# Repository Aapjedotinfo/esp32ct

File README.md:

# ESP32CT

**16-channel CT-clamp energy monitor with P1 in/out** (ESP32, ESPHome, KiCad), and a bit of help of Claude.

[Hardware](#hardware-overview) · [Mount](#mount-3d-printed) · [Firmware](#firmware-esphome) ·
[Calibration](#calibrating-the-ct-channels) · [Build it](#building-the-board) ·
[Open points](#status-and-known-open-points) · [Support](#support-the-project)

## What it is

A through-hole PCB that turns an ESP32 into a whole-house energy monitor for
[ESPHome](https://esphome.io) and Home Assistant. Clip a current clamp on each circuit in your
meter cupboard and see what your dryer, oven, EV charger and heat pump use separately.

- **16 CT-clamp channels** through one CD74HC4067 analog multiplexer and the ESP32's ADC
- **P1 input** (RJ12) to read a Dutch/Belgian smart meter (DSMR)
- **P1 output** (RJ12) that imitates a smart meter, so an EV charger can be load-balanced
  against values you choose (developed against an Alfen charger)
- **Water meter** pulse input (inductive 5 V NPN sensor)
- **Doorbell** button input and two relay outputs via an external relay board

It started as a hand-wired board in a meter cupboard and was redesigned as rev C, a
115 × 103 mm two-layer board that anyone can order and assemble with through-hole parts only.
Free to use; if it helps you and you would like to support future projects you can
[donate via aapje.info](https://aapje.info/donations/), never required.

More views: [bottom render](hardware/esp32ct-revc/render_bottom.png), the
[schematic](hardware/esp32ct-revc/esp32ct-revc.pdf) and the
[placement drawing](hardware/esp32ct-revc/plaatsing.pdf). A photo of the installation
(clamps on the distribution board) is still to be added.

## Why this design

- **Universal channels.** All 16 channels are identical. Which circuit is clamped on
  which channel is wiring and firmware, not silkscreen.
- **Burden resistor with a jumper per channel.** Each channel has a 33 Ω burden in
  series with a jumper. Closed: bare ring CT (e.g. GTA20L1.0, 1000:1). Open: a clamp
  with a built-in burden (e.g. SCT013-015 or -050). A jumper *across* the burden would
  short the clamp, so it is wired in series.
- **Short, quiet measurement loops.** CT terminals sit opposite each other along the
  two long edges, each with its burden and jumper directly behind it.
- **1.65 V mid-rail** from an LM358 voltage follower as the bias for all channels.
- **Everything external on screw terminals** (5.00 mm), except the two RJ12 jacks.
- **Fusing.** F1 protects the whole 5 V supply; F2 (200 mA) protects the 5 V on the
  P1-output pin so a short in the charger cable does not take the board down.
- **No strapping pins in use.** The multiplexer's S1 line is on GPIO4, not GPIO12
  (a strapping pin that can stop the module from booting). A check fails the build if
  anything is ever connected to GPIO0/2/5/12/15.

## Hardware overview

| Item | Detail |
|---|---|
| Board | 115 × 103 mm, 2 layers, FR4 1.6 mm, HASL, 4 × M3 holes |
| MCU | ESP32 D1-mini-style module (footprint of the MH-ET Live MiniKit, `mhetesp32minikit`; the prototype uses an AZ-Delivery ESP32-WROOM-32 of the same form factor), at the right edge with the antenna pointing outward and a copper keep-out under it |
| Mux | HW-178 CD74HC4067 breakout, plugged into two female headers (15.24 mm row spacing) |
| CT channels | 16 × 2-pole screw terminal (YIXISI, 5.00 mm), 33 Ω burden + jumper each |
| Power | 5 V in on a screw terminal, 1 A slow fuse |
| P1 in | RJ12, BC547 inverter to GPIO18, data request on GPIO23 |
| P1 out | RJ12, GPIO17 through a BC547 inverter to an open-collector line with 4k7 pull-up to 5 V |
| Water | 5 V inductive NPN sensor, pulse on GPIO32 with 10k pull-up to 3.3 V |
| Relays | Not on the board; a two-channel Arduino relay board connects with four wires |

Full pin map: [`hardware/PINMAPPING.md`](hardware/PINMAPPING.md).

### Pin summary

| GPIO | Function |
|---|---|
| 13 / 4 / 14 / 27 | Multiplexer address S0 / S1 / S2 / S3 |
| 34 | Multiplexer signal (ADC1) |
| 18 / 23 | P1 in: RX / data request |
| 17 / 16 | P1 out: TX / data request from the charger (optional) |
| 32 | Water meter pulse |
| 33 / 25 | Doorbell relay house / garage (active low) |
| 26 | Doorbell button |

## Mount (3D printed)

The board and the external relay board sit on a printed base plate with four conical
standoffs for the main board (brass heat-set inserts) and posts for the relay board.
Latest version: **R13 "kastgaten"** (holes for the enclosure screws, 4 mm, 158 × 90 mm
pitch), 190 × 110 × 31 mm, designed in Fusion.

| File | What |
|---|---|
| [`3dhouse/ESP32CT_PCB_houder_R13_kastgaten.stl`](3dhouse/ESP32CT_PCB_houder_R13_kastgaten.stl) | print this |
| [`3dhouse/ESP32CT_PCB_houder_R13_kastgaten.step`](3dhouse/ESP32CT_PCB_houder_R13_kastgaten.step) | editable solid for any CAD program |
| [`3dhouse/ESP32CT_PCB_houder_R13_kastgaten.f3d`](3dhouse/ESP32CT_PCB_houder_R13_kastgaten.f3d) | Fusion source with the feature timeline |
| [`3dhouse/PCB Holder v5.stl`](3dhouse/PCB%20Holder%20v5.stl) | earlier version (v5), 190 × 110 × 43 mm |

**Enclosure:** the prototype lives in this junction box (clear lid):
[Amazon.nl listing](https://www.amazon.nl/Aansluitdoos-aansluitdozen-elektronicaprojectdoos-aansluitkast-transparante/dp/B0CZ6CYHLS).
The holder is made to fit it; check the inner dimensions of the box you buy against the model
before printing.

The printed holder (black, ribbed baseplate) in the enclosure. The four board standoffs
carry brass heat-set inserts, and the relay board sits on its own posts at the top.
Which exact version is shown in the photo is not recorded.

## The PCB is generated, not drawn

Schematic, netlist, placement, routing and Gerbers are all produced by scripts in
[`hardware/`](hardware/) with KiCad 10 and Freerouting:

```bash
bash build.sh
```

This regenerates the schematic, checks the netlist, runs ERC, places and routes the
board, runs DRC, and exports drawings, BOM and Gerbers. The checks it runs itself
(netlist, layout) stop the build on failure. Errors reported by KiCad's export steps are
not yet caught (known issue), so check the ERC/DRC reports and the Gerbers before
ordering. Result of the last full run: **0 ERC, 0 DRC, 0 unconnected items.**

Do not edit the KiCad files by hand or save from KiCad: the next build overwrites them.
Change the scripts (`sheets.py` for the schematic, `pcb.py` for placement) instead.

### Checks that exist because something went wrong

`check_net.py` verifies more than "the schematic agrees with itself":

- the ADC pin, the address bus, all sixteen CT chains, the bias rail, and that every
  burden jumper is in series, not in parallel;
- a list of pins that may float; everything else unconnected is an error;
- a **physical pin assignment** block that enforces the real pinout of the real parts
  (LM358, BC547, HW-178), with the source of each.

That last block exists because, during design, three symbols turned out to have
invented pin numbers (CD74HC4067, LM358, BC547). The schematic was consistent, ERC was
clean, and the board would never have worked. If you reuse the symbols, read
[`hardware/OPEN_PUNTEN.md`](hardware/OPEN_PUNTEN.md).

## Firmware (ESPHome)

The reference configuration is [`firmware/esp32ct-revc.yaml`](firmware/esp32ct-revc.yaml) (copy `firmware/secrets.yaml.example` to `secrets.yaml` first). Highlights:

- One shared `cd74hc4067` hub on GPIO13/4/14/27 with the ADC on GPIO34. Two hubs on the
  same address lines break each other's pin cache and give impossible readings.
- Per ring channel: moving average first (window 6), then quadratic noise subtraction
  `sqrt(measured² − floor²)`, then `calibrate_linear`, then a low cut-off. The order
  matters: smoothing must come before the subtraction.
- DSMR/P1 reader, water meter (`pulse_meter`), gas total, doorbell with mute switches.
- **P1 output.** Number entities on the device (`P1 Out …`): signed power per phase
  (negative = export), tariff, fallback voltage and four kWh counters. Every second it
  builds a DSMR 5 telegram with CRC-16/ARC and writes it to UART2 on GPIO17 (115200
  8N1, *not* inverted in software; the transistor does that). Voltage comes from the
  real P1 input when valid. The output only transmits while the switch `P1 Out Aan` is
  on. After a reboot it returns to the last chosen state (by design), so a board that was
  transmitting keeps transmitting.

CT calibration curves and noise floors in the configuration belong to one installation
(ring CTs with 33 Ω, about 0.031 V/A fitted). **Measure your own.**

## Calibrating the CT channels

The board measures the voltage across the burden, not current. Firmware turns that
voltage into amperes per channel. Procedure used in this project:

1. **Start from the theoretical sensitivity** (volts per ampere at the ADC input):

   | Clamp | V/A |
   |---|---|
   | ring 1000:1 with 33 Ω burden (jumper closed) | 0.033 theoretical, about 0.031 fitted |
   | SCT013-015 (15 A / 1 V, built-in burden, jumper open) | 0.067 |
   | SCT013-050 (50 A / 1 V), one pass of the conductor | 0.02 |
   | SCT013-050, two passes (both in the same direction, insulated wire only) | 0.04 |

   Amps = measured volts ÷ V/A (for the 50 A clamp: ÷ (0.02 × number of passes)).
   These are theoretical values; real clamps deviate, so always measure.
2. **Measure the noise floor** with the conductor carrying no load: take the RMS
   reading of the channel (volts). On this installation about 0.042 V on the ring
   channels, which is roughly 1.4 A. Higher sensitivity clamps give a lower floor in
   amps (about 0.6 A for the 15 A clamp), but the floor is installation dependent.
3. **Filter order matters:** moving average first, then quadratic noise subtraction
   `signal = sqrt(measured² − floor²)`, then the linear calibration, then a cut-off
   (0.04 A here). Subtracting before smoothing works on an unstable value and gives
   unusable results.
4. **Fit the curve with known loads.** Switch on a load whose current you know or can
   measure with a reference (a plug-in energy meter or a Shelly, in this project) and
   read the channel's smoothed voltage. Use several loads across the range and enter
   the pairs in ESPHome as `calibrate_linear` points (voltage → amps), for example
   0.006 → 0, 0.109 → 3.45, 0.178 → 5.19, 0.263 → 8.48 for one ring channel.
5. **Re-check after any change** of clamp, burden or jumper. Closed or open jumper
   gives a completely different curve.
6. **Power** is `current × 230 V`. There is no voltage measurement and no phase
   information, so power factor is ignored and **direction cannot be seen**. A group
   with both load and generation shows the difference.

The ADC of an ESP32 is not linear near its limits; stay well within the clamp's range
for the channel (see the table below) and calibrate at the currents you care about.

| Clamp | Approximate range at the ADC |
|---|---|
| ring with 33 Ω | about 35 A |
| SCT013-015 | about 17 A |
| SCT013-050, one pass | about 58 A |
| SCT013-050, two passes | about 29 A |

Ranges and noise floors for the SCT013 clamps are estimates, not measurements.

## Building the board

**Ordering.** The Gerbers work with any PCB fab. Disclosure: I use [Aisler](https://aisler.net)
and earn shop credit when you order through my referral code `MakeInEurope-VYPFM` (you get
€10 off your first order). This is not an endorsement by Aisler.

1. Order `esp32ct-revc-gerbers.zip` from any fabricator (2 layers, 1.6 mm, HASL).
2. Check before you order, see [`hardware/OPEN_PUNTEN.md`](hardware/OPEN_PUNTEN.md):
   - row spacing of your HW-178 (15.24 mm)
   - wire entry direction and width of your screw terminals (≤ 10.7 mm per block;
     terminals sit on a 10.795 mm pitch)
   - GPIO16/17 on your MiniKit
   - that your relay board switches properly at 3.3 V on IN
3. Flash the ESP32 over USB **before** the HW-178 goes in; the USB connector is blocked
   afterwards. Later updates go over the air.
4. For clamps with a built-in burden (SCT013) leave the channel jumper **open**; for
   ring CTs close it. A channel with no clamp should keep its jumper **closed**,
   otherwise the mux input floats.

## Network security

The example configuration has no OTA password and no web-server login, which is common
on a trusted home network. Anyone who can reach the device can update its firmware and
operate it. Add `password:` to `ota` and `auth:` to `web_server` (with entries in your
`secrets.yaml`) if your network is not trusted.

## Documentation language

The README is in English. The detailed hardware notes in `hardware/` (`README.md`,
`OPEN_PUNTEN.md`, `PINMAPPING.md`, `PCB_BESCHRIJVING.md`) are still in Dutch; translations
are welcome. Silkscreen text on the board is Dutch too.

## Status and known open points

Rev C has been built and is running, but this is a hobby project made for one house.
Honestly open:

- The firmware builds a DSMR 5 telegram with CRC-16/ARC for the P1 output, but the
  actual output signal, a loopback test into the board's own P1 input, and
  acceptance by the EV charger are all **unverified**.
- A CT sees magnitude only, not direction. A circuit with both load and generation
  (e.g. solar on the same group) reads the *difference*.
- Some values in the power and P1 sheets are conventional designs, not measured from
  the original board: the 1.65 V divider, LM358 supply (3.3 V vs 5 V), bulk
  capacitors, the P1 inverter resistors, and whether P1 data-request may connect
  directly to a 3.3 V GPIO.
- Screw-terminal wire entry direction was derived from the footprint, not measured.
- Whether the charger expects DSMR 5 (115200 8N1) or DSMR 2/3 (9600 7E1).
- **Electrical safety.** The board itself only carries extra-low voltage, but CTs go
  around mains conductors; clamp only insulated conductors. A bare ring CT (1000:1,
  current output) with an open secondary develops dangerous voltage while primary
  current flows. On this board, opening a channel jumper (JP101-JP116) on a **ring-CT
  channel** is exactly that case: never open it while the conductor carries current.
  Only clamps with a built-in burden (SCT013 xA/1V) may have the jumper open.

## Repository layout

```
hardware/        KiCad generation scripts, checks, build.sh, docs
  esp32ct-revc/  generated KiCad project, Gerbers, drawings, BOM
  lib/           third-party footprints with provenance
firmware/        ESPHome configuration (rev C) and secrets.yaml.example
3dhouse/         3D-printable mount (STL)
```

## Licence

See [`LICENSE.md`](LICENSE.md).

| Part | Licence |
|---|---|
| Hardware, documentation, photos, 3D mount | [CERN-OHL-W-2.0](https://ohwr.org/cern_ohl_w_v2.txt) |
| Firmware (`firmware/`) | MIT |
| Third-party parts in `hardware/lib/` | their own licences (see Credits) |

You may build, use, modify and sell boards from these files. Changes to the hardware
design must be shared under the same licence. The hardware is provided without any
warranty; you are responsible for safe installation on your own mains wiring.

## Support the project

This board is a hobby project, free to use. If it saved you time or money and you
would like to help fund future projects, a donation is very welcome (never required):

- Donate via [aapje.info/donations](https://aapje.info/donations/)

Building a board and reporting what you found (photos, measurements, fixes) helps
just as much: please open an issue or a pull request.

## Credits and third-party material

- ESP32 MiniKit footprint from
  [r0oland/ESP32_mini_KiCad_Library](https://github.com/r0oland/ESP32_mini_KiCad_Library)
  (Apache-2.0), copy and licence text in `hardware/lib/`.
- Screw-terminal footprint derived from KiCad's MaiXu MX126 with a tighter courtyard.
- Symbols for LM358 and BC547 verified against KiCad's own libraries; HW-178 pinout
  verified against SparkFun's board file.
- Built with KiCad 10, Freerouting and ESPHome.

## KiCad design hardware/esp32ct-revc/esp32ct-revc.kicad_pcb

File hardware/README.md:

# esp32ct — hardware

KiCad-project voor **rev C** van het CT-bord: schema, netlist en een volledig
gerout bord, tot en met de Gerbers voor de printfabriek. Rev C is rev B met de
waarden van alle onderdelen op de zeefdruk en een liggende F2; elektrisch en
qua pinbezetting zijn ze gelijk. Basis is het huidige
bord, gereconstrueerd uit de draaiende firmware en uit opgave van de eigenaar;
er lag geen eerder ontwerp.

Gebouwd en gecontroleerd met **KiCad 10.0.6**. `build.sh` pakt zelf de nieuwste
installatie die het vindt; zet `KICAD_DIR` als je een andere wilt afdwingen.
Let op: het bord wordt door pcbnew 10 weggeschreven in het 10-formaat en is
daarmee niet meer met KiCad 9 te openen. Het schema schrijft de generator zelf,
nog in het 9-formaat, en dat leest 10 probleemloos.

Lees `OPEN_PUNTEN.md` voordat je hier iets uit overneemt. Daarin staat wat
vaststaat, wat aangenomen is, en wat er verandert ten opzichte van het bord dat
er nu hangt.

Wat je niet over het hoofd moet zien:

- **Bestelklaar:** `esp32ct-revc/esp32ct-revc-gerbers.zip`. 115 × 103 mm,
  2 lagen, FR4 1,6 mm, HASL (loodvrij mag).
- **Meet eerst je HW-178 en een schroefklem na** — zie `OPEN_PUNTEN.md` voor
  wat je vóór het bestellen controleert. De klemmen staan vrijwel tegen elkaar.
- **De relais zitten op een los Arduino-relaisbordje.** Die zijn actief-laag;
  de firmware heeft dan `inverted: true` nodig, anders rinkelt de bel bij elke
  reboot.
- **16 kanalen, één multiplexer.** De laadpaal wordt voortaan via de
  nagebootste P1-uitgang gestuurd in plaats van met CT's gemeten.
- **Firmware voor rev C:** `PINMAPPING.md` heeft de pinbezetting per GPIO en
  per connector, en wat er in `firmware/esp32ct-revc.yaml` moet veranderen.

## Openen

```bash
"/c/Program Files/KiCad/10.0/bin/kicad.exe" esp32ct-revc/esp32ct-revc.kicad_pro
```

Of blader door `esp32ct-revc/esp32ct-revc.pdf` (schema) en `plaatsing.pdf`
(bord) als je alleen wilt kijken.

## Bladindeling

| Blad | Inhoud |
|---|---|
| 1 | Overzicht en ESP32 — de complete pinbezetting |
| 2 | Voeding en VBIAS — 5 V in, de 1,65 V middenrail |
| 3 | Multiplexer — voetje voor het HW-178-breakout (CD74HC4067) |
| 4 | CT-kanalen 1-16, elk met burden en jumper |
| 5 | P1 slimme meter — ingang vanaf de echte meter |
| 6 | Deurbel en watermeter |
| 7 | P1-uitgang naar de laadpaal |

Alle bladen zijn onderling verbonden met globale labels; er zijn geen
hiërarchische pinnen. Een net met dezelfde naam is overal hetzelfde net.

## Schema én PCB zijn gegenereerd, niet getekend

`gen_sch.py` bevat de symbolen en de KiCad-primitieven, `sheets.py` beschrijft
het schema, `pcb.py` de plaatsing. **Pas de KiCad-bestanden niet met de hand
aan** — wijzig het script en bouw opnieuw, anders is je wijziging bij de
volgende run weg.

Dat is bewust: zestien identieke kanalen met de hand tekenen én plaatsen is
foutgevoelig, en het ontwerp verandert nog. Nu is de bron van waarheid een
leesbare lijst.

```bash
python3 sheets.py && python3 check_net.py
```

`check_net.py` controleert de geëxporteerde netlist op de verbindingen die echt
moeten kloppen: de ADC-pin, de adresbus, alle zestien CT-ketens, de VBIAS-rail,
en of de burden-jumper wel in serie staat en niet parallel. Het faalt hard als
er iets niet klopt, zodat een fout in de generator niet stilletjes in het
ontwerp blijft staan.

Daarnaast staat er een lijst van pinnen die los **mogen** hangen. Alles wat
daarbuiten valt is een fout. Die controle is er niet voor niets: tijdens het
bouwen verbraken drie verbindingen stilletjes doordat een draad midden op een
andere draad eindigde. In KiCad verbindt dat niet — ook niet met een junction
erbij — en het schema zag er gewoon goed uit.

En er is een blok **fysieke pinbezetting**: welke pin van het échte onderdeel
op welk net hoort, met de bron erbij (KiCad's eigen symbolen voor de LM358 en
BC547, SparkFun's bordbestand voor het HW-178). Alle andere controles kijken
of het schema met zichzelf klopt; deze kijkt of het klopt met de onderdelen die
je erop soldeert. Hij bestaat omdat drie symbolen verzonnen pinnummers bleken
te hebben — zie `OPEN_PUNTEN.md`. Nagegaan door de oude fouten tijdelijk terug
te zetten: hij vangt ze alle drie.

## De PCB

`pcb.py` bouwt `esp32ct-revc.kicad_pcb` uit de netlist: bordomtrek, alle
footprints op hun plek, elk pad op het juiste net, netklassen, de
massavlakken, het antenneverbod, montagegaten en de zeefdruk. Daarna legt
`freeroute.py` de banen met Freerouting. Het bord wordt bij elke build vanaf
nul geplaatst en gerout; er zit geen handwerk in.

Beide scripts draaien op de Python van KiCad, niet die van het systeem, want
alleen die heeft `pcbnew`. `build.sh` regelt dat zelf.

Bord: **115 × 103 mm**, dubbelzijdig, alles doorstekend, 77 onderdelen plus
4 montagegaten (M3). De indeling:

| Waar | Wat |
|---|---|
| boven- en onderrand | 16 CT-klemmen, acht per zijde, met staande burden en jumper er direct achter; de belknop J6 als negende klem onderaan |
| linkerrand | POWER IN (J1, met zekering F1 erachter), WATER (J3/J9), RELAIS (J4/J5); de 1,65 V-middenrail erachter |
| midden | het HW-178-voetje, precies tussen de twee CT-rijen |
| rechterrand | de twee RJ12's onder elkaar (P1 INPUT boven, P1 OUTPUT onder), met hun P1-onderdelen ernaast (ook F2/JP1: 5 V naar P1 OUT); daaronder de ESP32 met de antenne naar buiten |

De CT-klemmen staan met opzet tegenover elkaar langs de lange zijden, met hun
burden en jumper er meteen achter. Zo blijft de lus van klem naar burden kort;
dat is de gevoelige plek in deze meting. De klemmen staan op 10,795 mm steek,
~0,3 mm tussen de bodies; daarvoor is er een eigen footprint met de courtyard
op de body (`lib/MX126_2P_5mm_krap`).

Onder de antenne van de ESP32 ligt een **verbodsgebied voor koper**, zodat de
massavlakken de WiFi niet verstikken.

### Banen en massa

Freerouting legt alle verbindingen, **ook GND als gewone banen**. Daarbovenop
ligt op beide lagen een GND-vlak. Freerouting krijgt die vlakken bewust niet
te zien: met een vlak erbij legt hij geen enkele GND-baan, en vielen er steeds
GND-pads op een eilandje tussen de signaalbanen. Blijft er toch een
GND-verbinding open, dan beslist de DRC na het gieten van de vlakken of die via
het vlak dicht is. Een open verbinding op elk ander net stopt de build.

Freerouting geeft niet elke run hetzelfde resultaat. Daarom draaien de DRC en
de controles bij elke build opnieuw, en telt een eerdere geslaagde run niet.

### Aannames over de randconnectoren

**Schroefklemmen:** de draadinvoer staat naar buiten, op de aanname dat die aan
de **+Y-kant** van de footprint zit. Dat volgt uit de footprint zelf — de pads
liggen 3,80 mm van die rand en 4,00 mm van de andere, en de fab-laag tekent
daar een aparte band — maar het is niet aan een echt blokje nagemeten. Klopt
het niet, zet `INVOER` bovenin `pcb.py` op `0` en alle klemmen draaien in één
keer om.

**RJ12's:** de stekker gaat er aan de +Y-kant in. Dat is wél zeker: de pinnen
zitten achterin, op Y = 0 tot 2,5 mm, en aan de pinkant kan geen stekker in.

## Alles opnieuw uitvoeren

```bash
bash build.sh
```

Dat genereert het schema, controleert de netlist, draait de ERC, plaatst en
rout het bord, draait de DRC, en maakt tekeningen, renders, stuklijst en
Gerbers. Het stopt bij de eerste fout: een ERC of DRC met ook maar één melding,
of een verbinding die open blijft, levert geen Gerbers op. De huidige stand:
**0 ERC-meldingen, 0 DRC-meldingen, 0 onverbonden items.**

Freerouting (en Java 25) staan gebruikersbreed in
`%LOCALAPPDATA%\Programs\freerouting`; zet `FREEROUTING_JAR` om een andere te
gebruiken. De oude eigen router `route.py` werkt nog, maar de build gebruikt
hem niet meer.

Had je het project open in KiCad: sluit het en open het opnieuw. **Sla niet op
vanuit KiCad** — dat schrijft over de gegenereerde bestanden heen, en bij de
volgende build is het weer weg.

## Gegenereerde bestanden

In `esp32ct-revc/` staan naast de schema- en bordbestanden ook:

| Bestand | Wat |
|---|---|
| `esp32ct-revc-gerbers.zip` | Gerbers + boorbestanden, dit upload je bij de fabriek |
| `productie/` | dezelfde bestanden los |
| `render_top.png`, `render_bottom.png` | 3D-aanzicht van beide kanten |
| `plaatsing.pdf`, `bovenkant.pdf`, `onderkant.pdf` | bordtekeningen; de onderkant gespiegeld |
| `esp32ct-revc.pdf` | het schema |
| `bom.csv` | stuklijst |
| `esp32ct-revc.net`, `erc.txt`, `drc.txt` | netlist en controlerapporten |

Die worden allemaal opnieuw gemaakt door `build.sh` en zijn dus geen handwerk.

De symbolen staan in `esp32ct.kicad_sym`, een projecteigen bibliotheek. Het
project verwijst daar via `sym-lib-table` naar, dus het opent op elke machine
zonder dat je iets hoeft te installeren.

## Onderdelen van derden

De footprint van de ESP32-module komt uit
[r0oland/ESP32_mini_KiCad_Library](https://github.com/r0oland/ESP32_mini_KiCad_Library),
Apache License 2.0. De bron staat in `lib/` samen met de licentietekst;
`sheets.py` kopieert hem naar `esp32ct.pretty/`.

Belangrijk gevolg: **de pinnummers van U1 zijn de echte padnummers van de
module, niet de GPIO-nummers.** GPIO34 is pad 11, GPIO35 is pad 7, GPIO13 is
pad 18, enzovoort. De vertaaltabel staat bovenaan `check_net.py` en in
`sheets.py` als `NET_PER_PAD`. Zonder die nummering sluit het symbool niet aan
op de footprint.

De klemmenblokken zijn het type dat de eigenaar op voorraad heeft: YIXISI
2-polig met **5,00 mm steek** (het blauwe KF301-type) — nadrukkelijk geen
5,08 mm. De footprint is een kopie van KiCad's MaiXu MX126 met een krappere
courtyard en zeefdruk; zie `lib/MX126_2P_5mm_krap.HERKOMST.txt`.

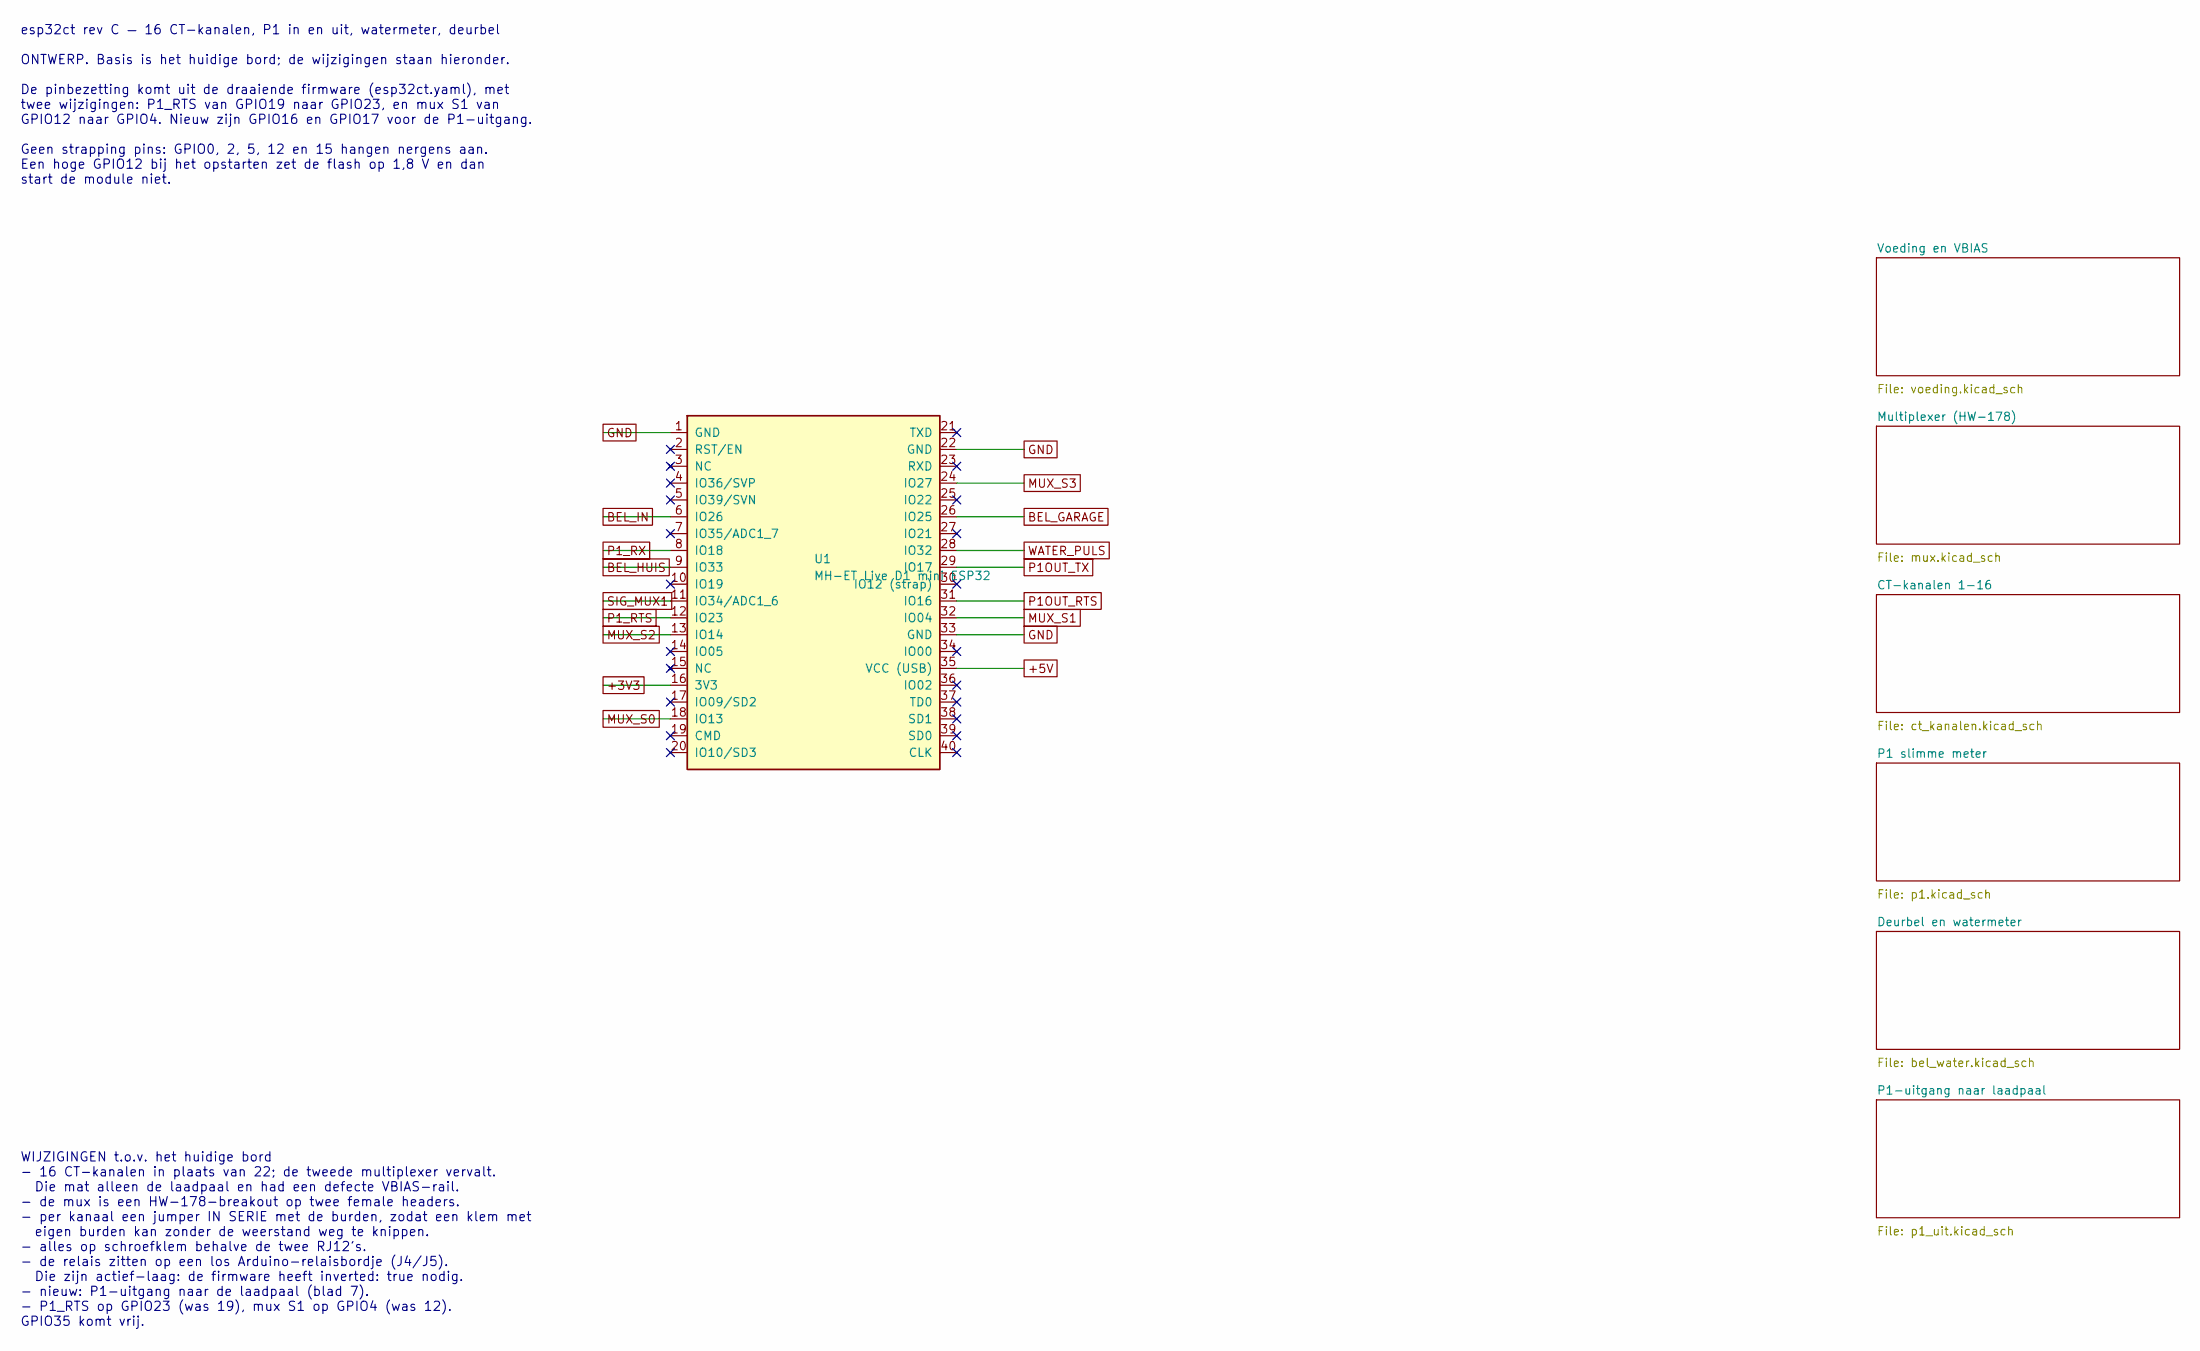
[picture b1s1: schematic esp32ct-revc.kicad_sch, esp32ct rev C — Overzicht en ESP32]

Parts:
U1: MH-ET Live D1 mini ESP32; ESP32_mini

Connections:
+3V3: U1.16 (3V3); also elsewhere on the board
+5V: U1.35 (VCC (USB)); also elsewhere on the board
BEL_GARAGE: U1.26 (IO25); also elsewhere on the board
BEL_HUIS: U1.9 (IO33); also elsewhere on the board
BEL_IN: U1.6 (IO26); also elsewhere on the board
GND: U1.1 (GND), U1.22 (GND), U1.33 (GND); also elsewhere on the board
MUX_S0: U1.18 (IO13); also elsewhere on the board
MUX_S1: U1.32 (IO04); also elsewhere on the board
MUX_S2: U1.13 (IO14); also elsewhere on the board
MUX_S3: U1.24 (IO27); also elsewhere on the board
P1OUT_RTS: U1.31 (IO16); also elsewhere on the board
P1OUT_TX: U1.29 (IO17); also elsewhere on the board
P1_RTS: U1.12 (IO23); also elsewhere on the board
P1_RX: U1.8 (IO18); also elsewhere on the board
SIG_MUX1: U1.11 (IO34/ADC1_6); also elsewhere on the board
WATER_PULS: U1.28 (IO32); also elsewhere on the board

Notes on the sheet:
esp32ct rev C — 16 CT-kanalen, P1 in en uit, watermeter, deurbel ONTWERP. Basis is het huidige bord; de wijzigingen staan hieronder. De pinbezetting komt uit de draaiende firmware (esp32ct.yaml), met twee wijzigingen: P1_RTS van GPIO19 naar GPIO23, en mux S1 van GPIO12 naar GPIO4. Nieuw zijn GPIO16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
WIJZIGINGEN t.o.v. het huidige bord - 16 CT-kanalen in plaats van 22; de tweede multiplexer vervalt. Die mat alleen de laadpaal en had een defecte VBIAS-rail. - de mux is een HW-178-breakout op twee female headers. - per kanaal een jumper IN SERIE met de burden, zodat een klem met eigen burden kan 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

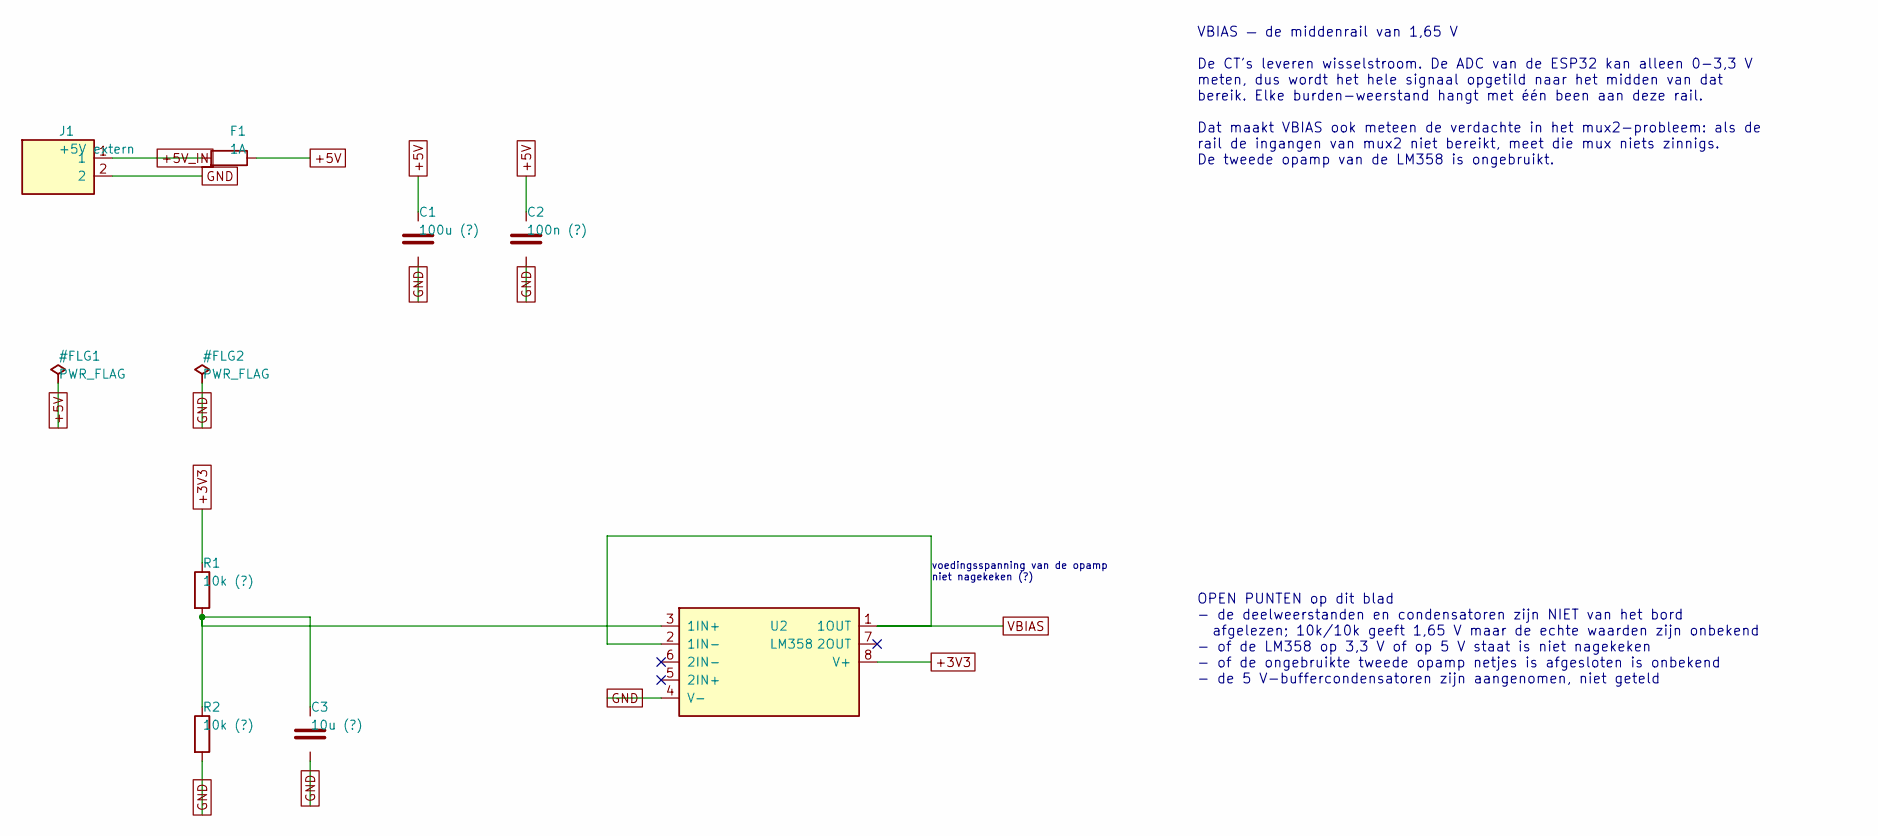
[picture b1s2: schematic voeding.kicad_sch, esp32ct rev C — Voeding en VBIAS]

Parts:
C1: 100u (?); CP_Radial_D6.3mm_P2.50mm
C2: 100n (?); C_Disc_D5.0mm_W2.5mm_P5.00mm
C3: 10u (?); CP_Radial_D6.3mm_P2.50mm
F1: 1A; R_Axial_DIN0207_L6.3mm_D2.5mm_P10.16mm_Horizontal
J1: +5V extern; MX126_2P_5mm_krap
R1, R2: 10k (?); R_Axial_DIN0207_L6.3mm_D2.5mm_P10.16mm_Horizontal
U2: LM358; DIP-8_W7.62mm

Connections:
+3V3: R1.1, U2.8 (V+); also elsewhere on the board
+5V: C1.1, C2.1, F1.2; also elsewhere on the board
+5V_IN: F1.1, J1.1
GND: C1.2, C2.2, C3.2, J1.2, R2.2, U2.4 (V-); also elsewhere on the board
unnamed: C3.1, R1.2, R2.1, U2.3 (1IN+)
VBIAS: U2.1 (1OUT), U2.2 (1IN-); also elsewhere on the board

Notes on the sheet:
voedingsspanning van de opamp niet nagekeken (?)
VBIAS — de middenrail van 1,65 V De CT's leveren wisselstroom. De ADC van de ESP32 kan alleen 0-3,3 V meten, dus wordt het hele signaal opgetild naar het midden van dat bereik. Elke burden-weerstand hangt met één been aan deze rail. Dat maakt VBIAS ook meteen de verdachte in het mux2-probleem: als 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
OPEN PUNTEN op dit blad - de deelweerstanden en condensatoren zijn NIET van het bord afgelezen; 10k/10k geeft 1,65 V maar de echte waarden zijn onbekend - of de LM358 op 3,3 V of op 5 V staat is niet nagekeken - of de ongebruikte tweede opamp netjes is afgesloten is onbekend - de 5 V-buffercondensa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

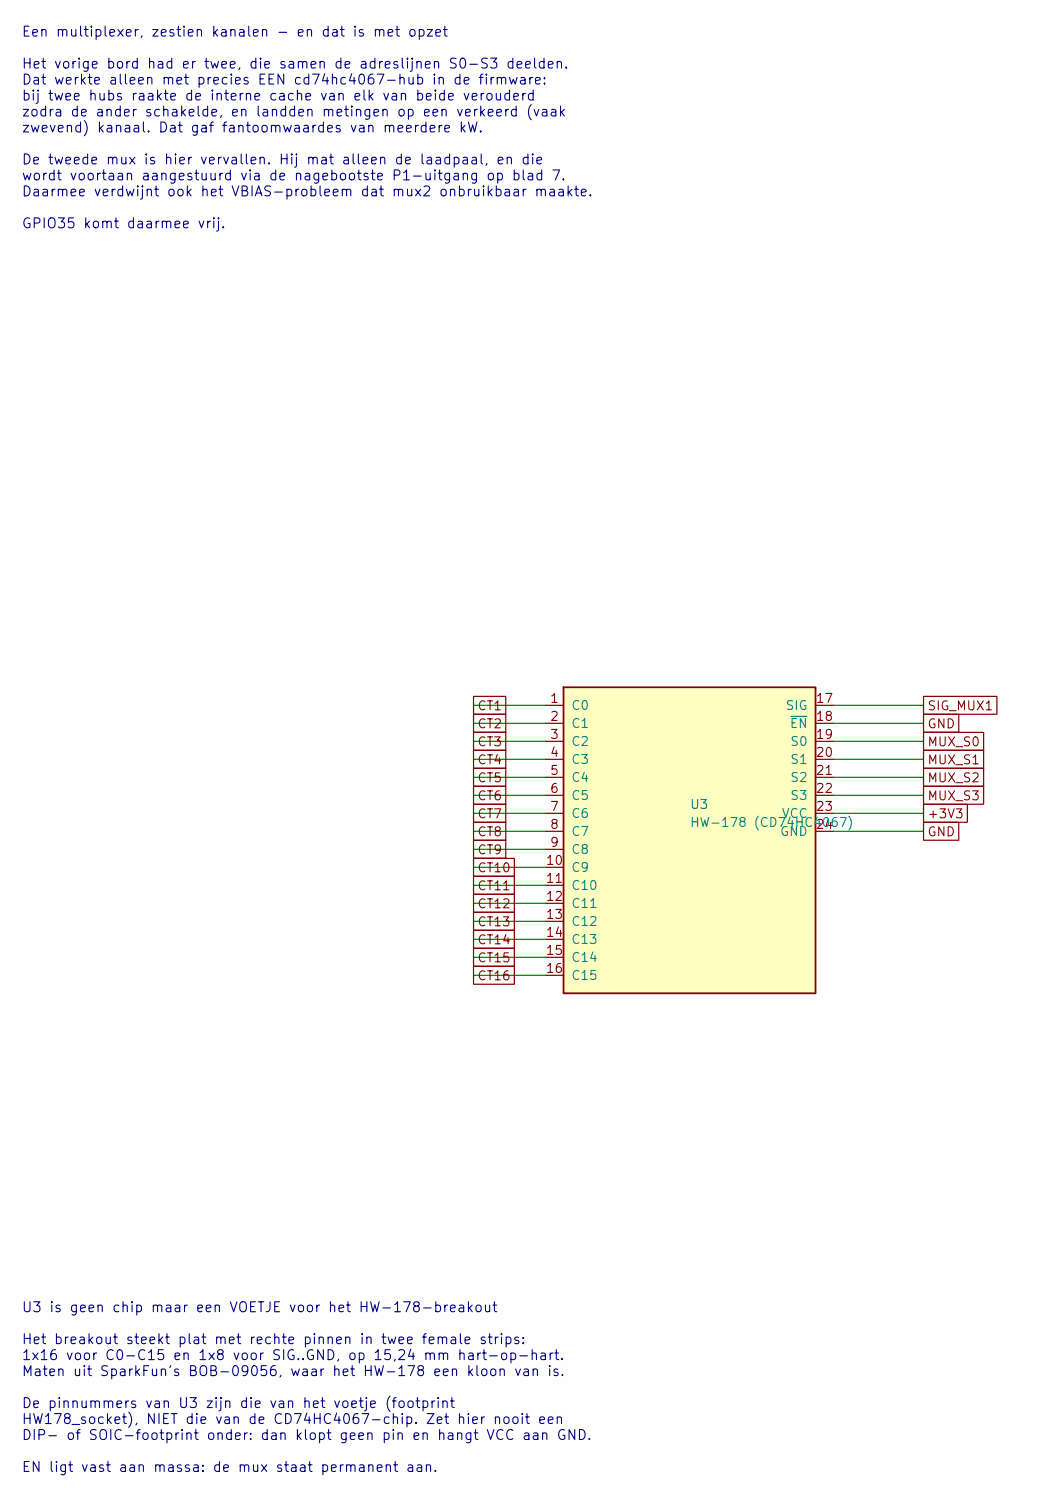
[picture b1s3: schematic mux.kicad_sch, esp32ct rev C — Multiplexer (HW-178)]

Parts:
U3: HW-178 (CD74HC4067); HW178_socket

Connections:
+3V3: U3.23 (VCC); also elsewhere on the board
CT1: U3.1 (C0); also elsewhere on the board
CT2: U3.2 (C1); also elsewhere on the board
CT3: U3.3 (C2); also elsewhere on the board
CT4: U3.4 (C3); also elsewhere on the board
CT5: U3.5 (C4); also elsewhere on the board
CT6: U3.6 (C5); also elsewhere on the board
CT7: U3.7 (C6); also elsewhere on the board
CT8: U3.8 (C7); also elsewhere on the board
CT9: U3.9 (C8); also elsewhere on the board
CT10: U3.10 (C9); also elsewhere on the board
CT11: U3.11 (C10); also elsewhere on the board
CT12: U3.12 (C11); also elsewhere on the board
CT13: U3.13 (C12); also elsewhere on the board
CT14: U3.14 (C13); also elsewhere on the board
CT15: U3.15 (C14); also elsewhere on the board
CT16: U3.16 (C15); also elsewhere on the board
GND: U3.18 (~EN), U3.24 (GND); also elsewhere on the board
MUX_S0: U3.19 (S0); also elsewhere on the board
MUX_S1: U3.20 (S1); also elsewhere on the board
MUX_S2: U3.21 (S2); also elsewhere on the board
MUX_S3: U3.22 (S3); also elsewhere on the board
SIG_MUX1: U3.17 (SIG); also elsewhere on the board

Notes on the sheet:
Een multiplexer, zestien kanalen - en dat is met opzet Het vorige bord had er twee, die samen de adreslijnen S0-S3 deelden. Dat werkte alleen met precies EEN cd74hc4067-hub in de firmware: bij twee hubs raakte de interne cache van elk van beide verouderd zodra de ander schakelde, en landden metinge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
U3 is geen chip maar een VOETJE voor het HW-178-breakout Het breakout steekt plat met rechte pinnen in twee female strips: 1x16 voor C0-C15 en 1x8 voor SIG..GND, op 15,24 mm hart-op-hart. Maten uit SparkFun's BOB-09056, waar het HW-178 een kloon van is. De pinnummers van U3 zijn die van het voetje 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

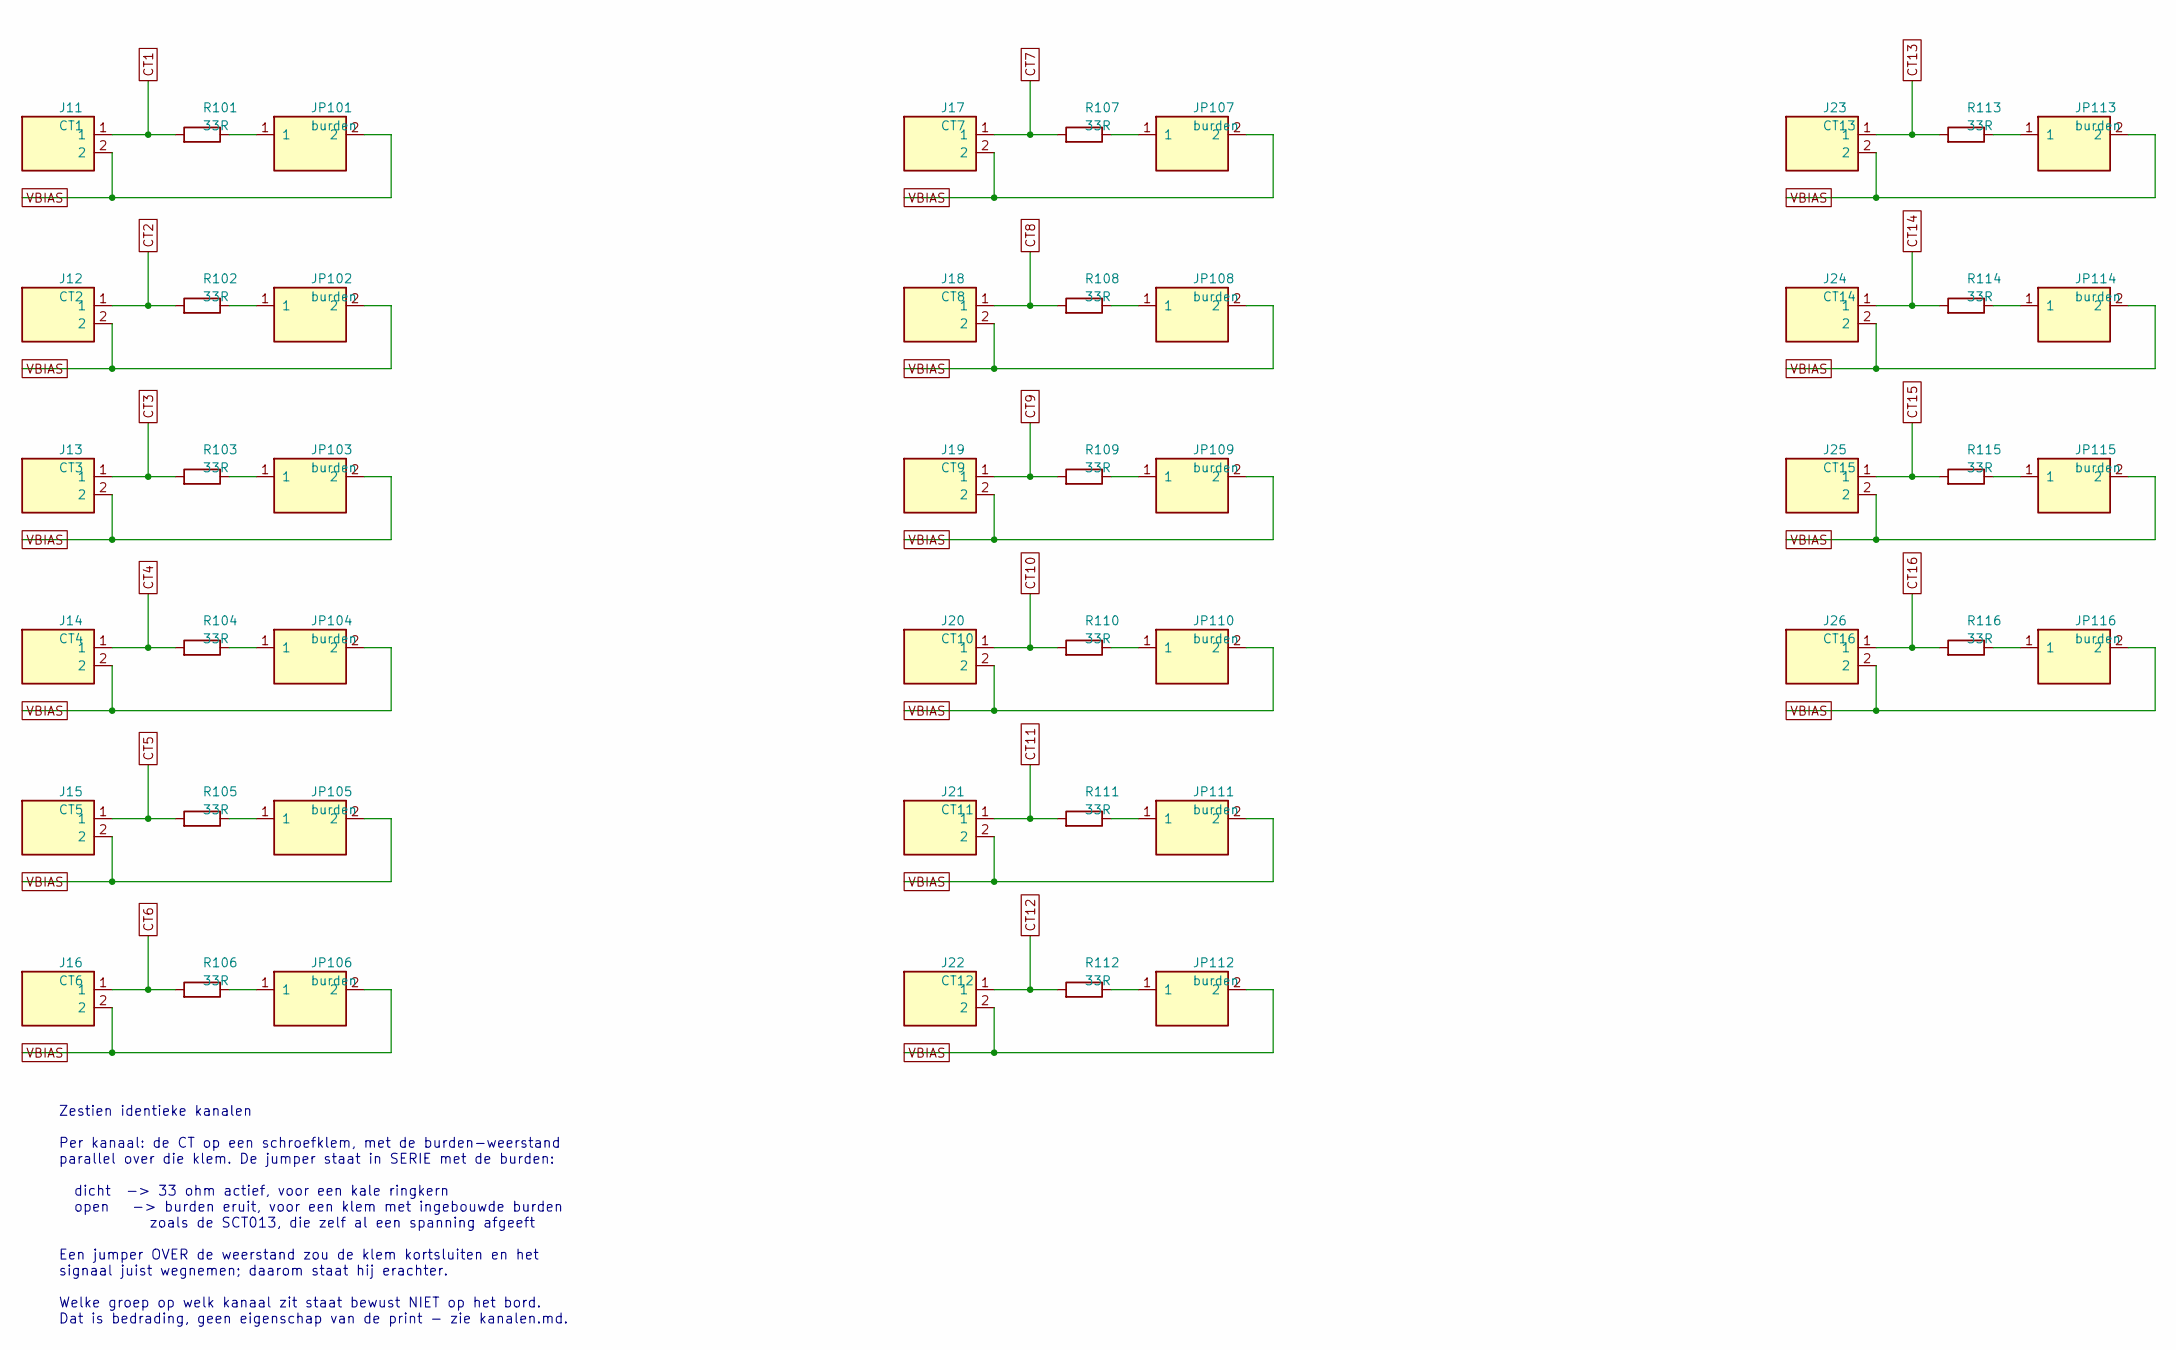
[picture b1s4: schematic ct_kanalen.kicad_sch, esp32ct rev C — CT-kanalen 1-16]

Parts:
J11: CT1; MX126_2P_5mm_krap
J12: CT2; MX126_2P_5mm_krap
J13: CT3; MX126_2P_5mm_krap
J14: CT4; MX126_2P_5mm_krap
J15: CT5; MX126_2P_5mm_krap
J16: CT6; MX126_2P_5mm_krap
J17: CT7; MX126_2P_5mm_krap
J18: CT8; MX126_2P_5mm_krap
J19: CT9; MX126_2P_5mm_krap
J20: CT10; MX126_2P_5mm_krap
J21: CT11; MX126_2P_5mm_krap
J22: CT12; MX126_2P_5mm_krap
J23: CT13; MX126_2P_5mm_krap
J24: CT14; MX126_2P_5mm_krap
J25: CT15; MX126_2P_5mm_krap
J26: CT16; MX126_2P_5mm_krap
JP101, JP102, JP103, JP104, JP105, JP106, JP107, JP108, JP109, JP110, JP111, JP112, JP113, JP114, JP115, JP116: burden; PinHeader_1x02_P2.54mm_Vertical
R101, R102, R103, R104, R105, R106, R107, R108, R109, R110, R111, R112, R113, R114, R115, R116: 33R; R_Axial_DIN0207_L6.3mm_D2.5mm_P2.54mm_Vertical

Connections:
CT1: J11.1, R101.1; also elsewhere on the board
CT2: J12.1, R102.1; also elsewhere on the board
CT3: J13.1, R103.1; also elsewhere on the board
CT4: J14.1, R104.1; also elsewhere on the board
CT5: J15.1, R105.1; also elsewhere on the board
CT6: J16.1, R106.1; also elsewhere on the board
CT7: J17.1, R107.1; also elsewhere on the board
CT8: J18.1, R108.1; also elsewhere on the board
CT9: J19.1, R109.1; also elsewhere on the board
CT10: J20.1, R110.1; also elsewhere on the board
CT11: J21.1, R111.1; also elsewhere on the board
CT12: J22.1, R112.1; also elsewhere on the board
CT13: J23.1, R113.1; also elsewhere on the board
CT14: J24.1, R114.1; also elsewhere on the board
CT15: J25.1, R115.1; also elsewhere on the board
CT16: J26.1, R116.1; also elsewhere on the board
unnamed: JP101.1, R101.2
unnamed: JP102.1, R102.2
unnamed: JP103.1, R103.2
unnamed: JP104.1, R104.2
unnamed: JP105.1, R105.2
unnamed: JP106.1, R106.2
unnamed: JP107.1, R107.2
unnamed: JP108.1, R108.2
unnamed: JP109.1, R109.2
unnamed: JP110.1, R110.2
unnamed: JP111.1, R111.2
unnamed: JP112.1, R112.2
unnamed: JP113.1, R113.2
unnamed: JP114.1, R114.2
unnamed: JP115.1, R115.2
unnamed: JP116.1, R116.2
VBIAS: J11.2, J12.2, J13.2, J14.2, J15.2, J16.2, J17.2, J18.2, J19.2, J20.2, J21.2, J22.2, J23.2, J24.2, J25.2, J26.2, JP101.2, JP102.2, JP103.2, JP104.2, JP105.2, JP106.2, JP107.2, JP108.2, JP109.2, JP110.2, JP111.2, JP112.2, JP113.2, JP114.2, JP115.2, JP116.2; also elsewhere on the board

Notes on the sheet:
Zestien identieke kanalen Per kanaal: de CT op een schroefklem, met de burden-weerstand parallel over die klem. De jumper staat in SERIE met de burden: dicht -> 33 ohm actief, voor een kale ringkern open -> burden eruit, voor een klem met ingebouwde burden zoals de SCT013, die zelf al een spanning 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

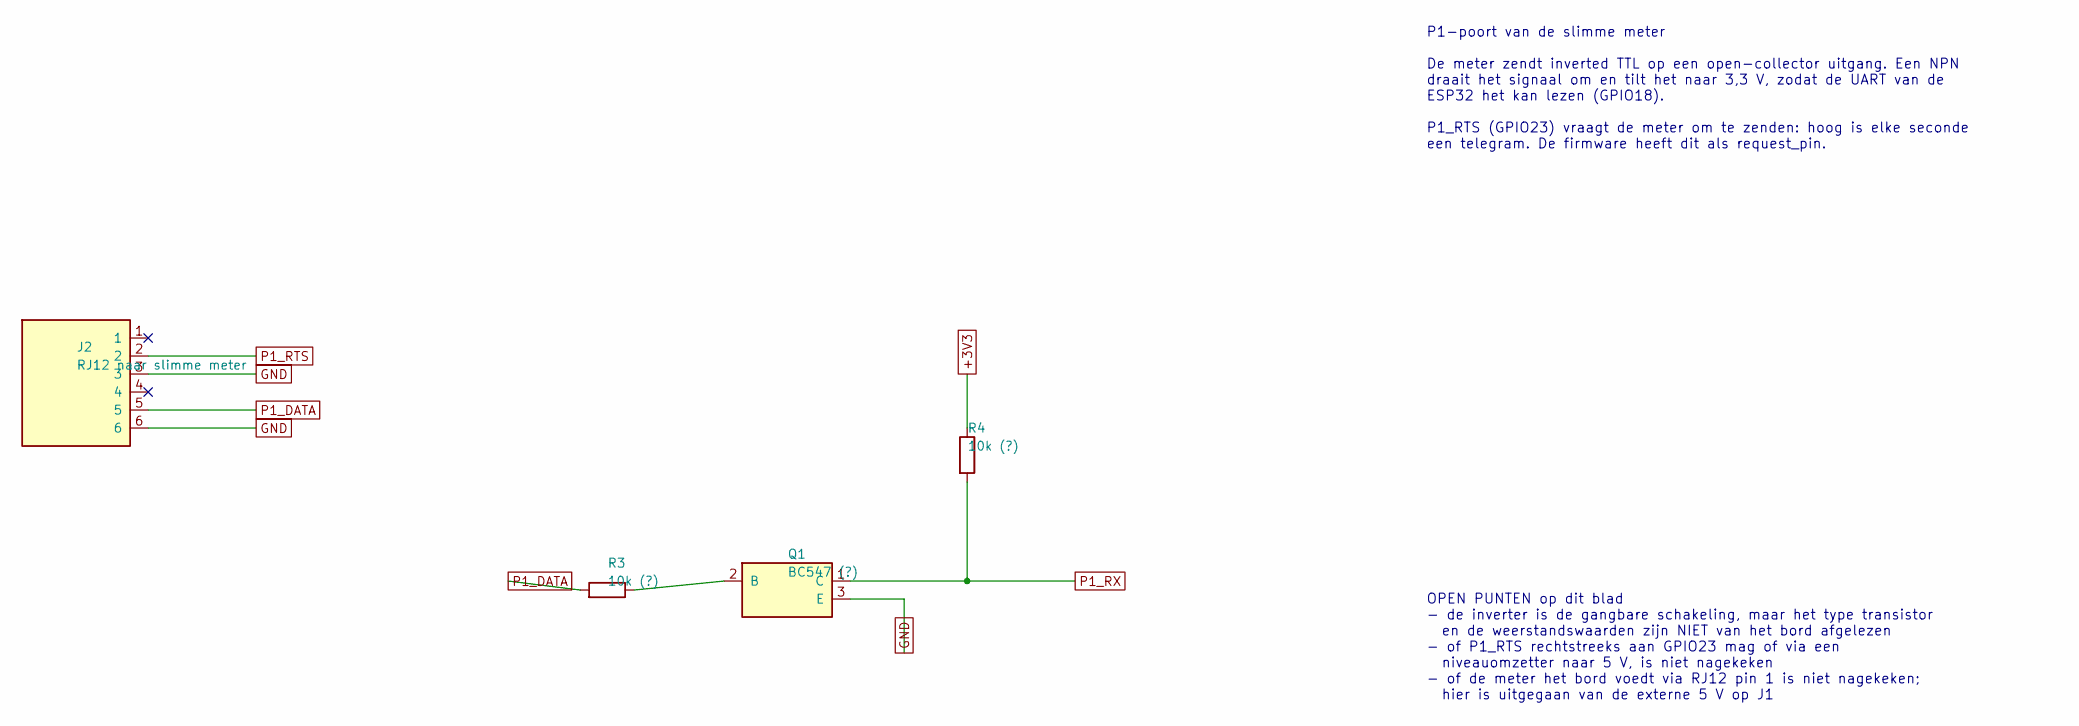
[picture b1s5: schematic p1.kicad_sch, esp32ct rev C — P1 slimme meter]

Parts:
J2: RJ12 naar slimme meter; RJ12_Amphenol_54601-x06_Horizontal
Q1: BC547 (?); TO-92_Inline_Wide
R3, R4: 10k (?); R_Axial_DIN0207_L6.3mm_D2.5mm_P10.16mm_Horizontal

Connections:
+3V3: R4.1; also elsewhere on the board
GND: J2.3, J2.6, Q1.3 (E); also elsewhere on the board
unnamed: Q1.2 (B), R3.2
P1_DATA: J2.5, R3.1
P1_RTS: J2.2; also elsewhere on the board
P1_RX: Q1.1 (C), R4.2; also elsewhere on the board

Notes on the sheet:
P1-poort van de slimme meter De meter zendt inverted TTL op een open-collector uitgang. Een NPN draait het signaal om en tilt het naar 3,3 V, zodat de UART van de ESP32 het kan lezen (GPIO18). P1_RTS (GPIO23) vraagt de meter om te zenden: hoog is elke seconde een telegram. De firmware heeft dit als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
OPEN PUNTEN op dit blad - de inverter is de gangbare schakeling, maar het type transistor en de weerstandswaarden zijn NIET van het bord afgelezen - of P1_RTS rechtstreeks aan GPIO23 mag of via een niveauomzetter naar 5 V, is niet nagekeken - of de meter het bord voedt via RJ12 pin 1 is niet nageke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

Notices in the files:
README.md:
Hardware: CERN-OHL-W-2.0
